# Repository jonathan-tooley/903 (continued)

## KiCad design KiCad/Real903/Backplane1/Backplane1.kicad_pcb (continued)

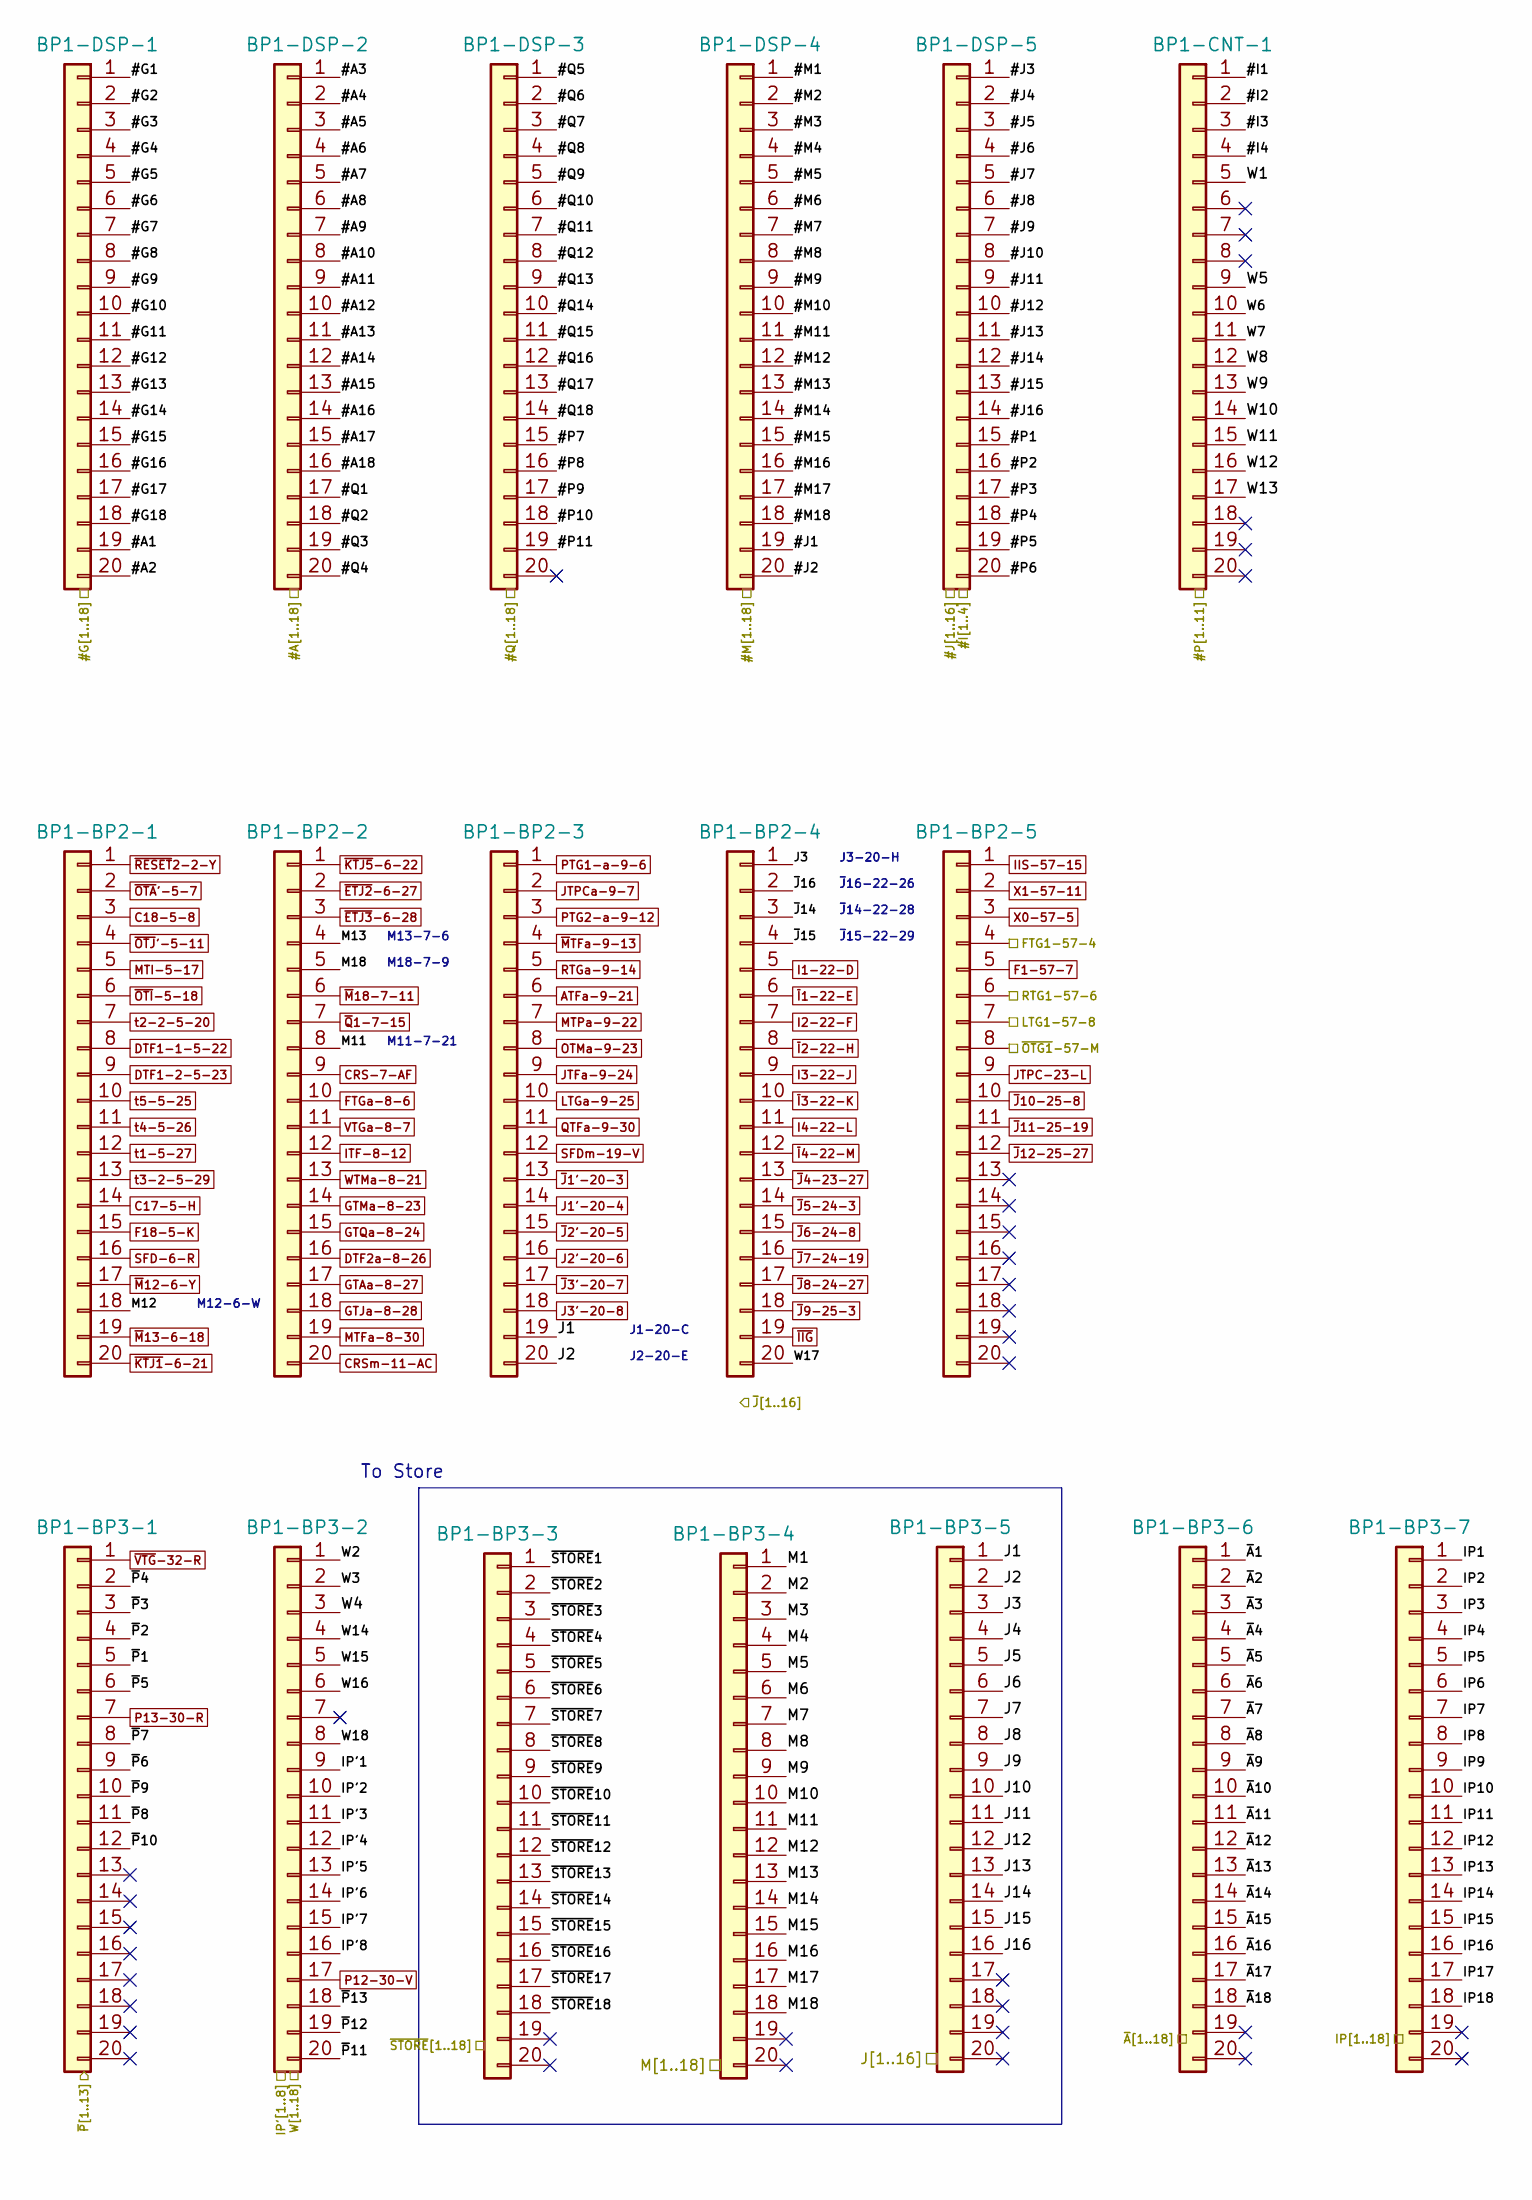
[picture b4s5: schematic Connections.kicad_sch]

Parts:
BP1-BP2-1, BP1-BP2-2, BP1-BP2-3, BP1-BP2-4, BP1-BP2-5, BP1-BP3-1, BP1-BP3-2, BP1-BP3-3, BP1-BP3-4, BP1-BP3-5, BP1-BP3-6, BP1-BP3-7, BP1-CNT-1, BP1-DSP-1, BP1-DSP-2, BP1-DSP-3, BP1-DSP-4, BP1-DSP-5: IDC-Header_2x10_P2.54mm_Latch_Vertical

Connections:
#A1: BP1-DSP-1.19; also elsewhere on the board
#A2: BP1-DSP-1.20; also elsewhere on the board
#A3: BP1-DSP-2.1; also elsewhere on the board
#A4: BP1-DSP-2.2; also elsewhere on the board
#A5: BP1-DSP-2.3; also elsewhere on the board
#A6: BP1-DSP-2.4; also elsewhere on the board
#A7: BP1-DSP-2.5; also elsewhere on the board
#A8: BP1-DSP-2.6; also elsewhere on the board
#A9: BP1-DSP-2.7; also elsewhere on the board
#A10: BP1-DSP-2.8; also elsewhere on the board
#A11: BP1-DSP-2.9; also elsewhere on the board
#A12: BP1-DSP-2.10; also elsewhere on the board
#A13: BP1-DSP-2.11; also elsewhere on the board
#A14: BP1-DSP-2.12; also elsewhere on the board
#A15: BP1-DSP-2.13; also elsewhere on the board
#A16: BP1-DSP-2.14; also elsewhere on the board
#A17: BP1-DSP-2.15; also elsewhere on the board
#A18: BP1-DSP-2.16; also elsewhere on the board
#G1: BP1-DSP-1.1; also elsewhere on the board
#G2: BP1-DSP-1.2; also elsewhere on the board
#G3: BP1-DSP-1.3; also elsewhere on the board
#G4: BP1-DSP-1.4; also elsewhere on the board
#G5: BP1-DSP-1.5; also elsewhere on the board
#G6: BP1-DSP-1.6; also elsewhere on the board
#G7: BP1-DSP-1.7; also elsewhere on the board
#G8: BP1-DSP-1.8; also elsewhere on the board
#G9: BP1-DSP-1.9; also elsewhere on the board
#G10: BP1-DSP-1.10; also elsewhere on the board
#G11: BP1-DSP-1.11; also elsewhere on the board
#G12: BP1-DSP-1.12; also elsewhere on the board
#G13: BP1-DSP-1.13; also elsewhere on the board
#G14: BP1-DSP-1.14; also elsewhere on the board
#G15: BP1-DSP-1.15; also elsewhere on the board
#G16: BP1-DSP-1.16; also elsewhere on the board
#G17: BP1-DSP-1.17; also elsewhere on the board
#G18: BP1-DSP-1.18; also elsewhere on the board
#I1: BP1-CNT-1.1; also elsewhere on the board
#I2: BP1-CNT-1.2; also elsewhere on the board
#I3: BP1-CNT-1.3; also elsewhere on the board
#I4: BP1-CNT-1.4; also elsewhere on the board
#J1: BP1-DSP-4.19; also elsewhere on the board
#J2: BP1-DSP-4.20; also elsewhere on the board
#J3: BP1-DSP-5.1; also elsewhere on the board
#J4: BP1-DSP-5.2; also elsewhere on the board
#J5: BP1-DSP-5.3; also elsewhere on the board
#J6: BP1-DSP-5.4; also elsewhere on the board
#J7: BP1-DSP-5.5; also elsewhere on the board
#J8: BP1-DSP-5.6; also elsewhere on the board
#J9: BP1-DSP-5.7; also elsewhere on the board
#J10: BP1-DSP-5.8; also elsewhere on the board
#J11: BP1-DSP-5.9; also elsewhere on the board
#J12: BP1-DSP-5.10; also elsewhere on the board
#J13: BP1-DSP-5.11; also elsewhere on the board
#J14: BP1-DSP-5.12; also elsewhere on the board
#J15: BP1-DSP-5.13; also elsewhere on the board
#J16: BP1-DSP-5.14; also elsewhere on the board
#M1: BP1-DSP-4.1; also elsewhere on the board
#M2: BP1-DSP-4.2; also elsewhere on the board
#M3: BP1-DSP-4.3; also elsewhere on the board
#M4: BP1-DSP-4.4; also elsewhere on the board
#M5: BP1-DSP-4.5; also elsewhere on the board
#M6: BP1-DSP-4.6; also elsewhere on the board
#M7: BP1-DSP-4.7; also elsewhere on the board
#M8: BP1-DSP-4.8; also elsewhere on the board
#M9: BP1-DSP-4.9; also elsewhere on the board
#M10: BP1-DSP-4.10; also elsewhere on the board
#M11: BP1-DSP-4.11; also elsewhere on the board
#M12: BP1-DSP-4.12; also elsewhere on the board
#M13: BP1-DSP-4.13; also elsewhere on the board
#M14: BP1-DSP-4.14; also elsewhere on the board
#M15: BP1-DSP-4.15; also elsewhere on the board
#M16: BP1-DSP-4.16; also elsewhere on the board
#M17: BP1-DSP-4.17; also elsewhere on the board
#M18: BP1-DSP-4.18; also elsewhere on the board
#P1: BP1-DSP-5.15; also elsewhere on the board
#P2: BP1-DSP-5.16; also elsewhere on the board
#P3: BP1-DSP-5.17; also elsewhere on the board
#P4: BP1-DSP-5.18; also elsewhere on the board
#P5: BP1-DSP-5.19; also elsewhere on the board
#P6: BP1-DSP-5.20; also elsewhere on the board
#P7: BP1-DSP-3.15; also elsewhere on the board
#P8: BP1-DSP-3.16; also elsewhere on the board
#P9: BP1-DSP-3.17; also elsewhere on the board
#P10: BP1-DSP-3.18; also elsewhere on the board
#P11: BP1-DSP-3.19; also elsewhere on the board
#Q1: BP1-DSP-2.17; also elsewhere on the board
#Q2: BP1-DSP-2.18; also elsewhere on the board
#Q3: BP1-DSP-2.19; also elsewhere on the board
#Q4: BP1-DSP-2.20; also elsewhere on the board
#Q5: BP1-DSP-3.1; also elsewhere on the board
#Q6: BP1-DSP-3.2; also elsewhere on the board
#Q7: BP1-DSP-3.3; also elsewhere on the board
#Q8: BP1-DSP-3.4; also elsewhere on the board
#Q9: BP1-DSP-3.5; also elsewhere on the board
#Q10: BP1-DSP-3.6; also elsewhere on the board
#Q11: BP1-DSP-3.7; also elsewhere on the board
#Q12: BP1-DSP-3.8; also elsewhere on the board
#Q13: BP1-DSP-3.9; also elsewhere on the board
#Q14: BP1-DSP-3.10; also elsewhere on the board
#Q15: BP1-DSP-3.11; also elsewhere on the board
#Q16: BP1-DSP-3.12; also elsewhere on the board
#Q17: BP1-DSP-3.13; also elsewhere on the board
#Q18: BP1-DSP-3.14; also elsewhere on the board
/Connections/~J14: BP1-BP2-4.3; also elsewhere on the board
/Connections/~J15: BP1-BP2-4.4; also elsewhere on the board
/Connections/~J16: BP1-BP2-4.2; also elsewhere on the board
/Low.FTG: BP1-BP2-5.4; also elsewhere on the board
/Low.LTG: BP1-BP2-5.7; also elsewhere on the board
/Low.RTG: BP1-BP2-5.6; also elsewhere on the board
/Low.~OTG: BP1-BP2-5.8; also elsewhere on the board
ATFa-9-21: BP1-BP2-3.6; also elsewhere on the board
C17-5-H: BP1-BP2-1.14; also elsewhere on the board
C18-5-8: BP1-BP2-1.3; also elsewhere on the board
CRS-7-AF: BP1-BP2-2.9; also elsewhere on the board
CRSm-11-AC: BP1-BP2-2.20; also elsewhere on the board
DTF1-1-5-22: BP1-BP2-1.8; also elsewhere on the board
DTF1-2-5-23: BP1-BP2-1.9; also elsewhere on the board
DTF2a-8-26: BP1-BP2-2.16; also elsewhere on the board
F1-57-7: BP1-BP2-5.5; also elsewhere on the board
F18-5-K: BP1-BP2-1.15; also elsewhere on the board
FTGa-8-6: BP1-BP2-2.10; also elsewhere on the board
GTAa-8-27: BP1-BP2-2.17; also elsewhere on the board
GTJa-8-28: BP1-BP2-2.18; also elsewhere on the board
GTMa-8-23: BP1-BP2-2.14; also elsewhere on the board
GTQa-8-24: BP1-BP2-2.15; also elsewhere on the board
I1-22-D: BP1-BP2-4.5; also elsewhere on the board
I2-22-F: BP1-BP2-4.7; also elsewhere on the board
I3-22-J: BP1-BP2-4.9; also elsewhere on the board
I4-22-L: BP1-BP2-4.11; also elsewhere on the board
IIS-57-15: BP1-BP2-5.1; also elsewhere on the board
IP1: BP1-BP3-7.1; also elsewhere on the board
IP2: BP1-BP3-7.2; also elsewhere on the board
IP3: BP1-BP3-7.3; also elsewhere on the board
IP4: BP1-BP3-7.4; also elsewhere on the board
IP5: BP1-BP3-7.5; also elsewhere on the board
IP6: BP1-BP3-7.6; also elsewhere on the board
IP7: BP1-BP3-7.7; also elsewhere on the board
IP8: BP1-BP3-7.8; also elsewhere on the board
IP9: BP1-BP3-7.9; also elsewhere on the board
IP10: BP1-BP3-7.10; also elsewhere on the board
IP11: BP1-BP3-7.11; also elsewhere on the board
IP12: BP1-BP3-7.12; also elsewhere on the board
IP13: BP1-BP3-7.13; also elsewhere on the board
IP14: BP1-BP3-7.14; also elsewhere on the board
IP15: BP1-BP3-7.15; also elsewhere on the board
IP16: BP1-BP3-7.16; also elsewhere on the board
IP17: BP1-BP3-7.17; also elsewhere on the board
IP18: BP1-BP3-7.18; also elsewhere on the board
IP'1: BP1-BP3-2.9; also elsewhere on the board
IP'2: BP1-BP3-2.10; also elsewhere on the board
IP'3: BP1-BP3-2.11; also elsewhere on the board
IP'4: BP1-BP3-2.12; also elsewhere on the board
IP'5: BP1-BP3-2.13; also elsewhere on the board
IP'6: BP1-BP3-2.14; also elsewhere on the board
IP'7: BP1-BP3-2.15; also elsewhere on the board
IP'8: BP1-BP3-2.16; also elsewhere on the board
ITF-8-12: BP1-BP2-2.12; also elsewhere on the board
J1: BP1-BP2-3.19, BP1-BP3-5.1; also elsewhere on the board
J1'-20-4: BP1-BP2-3.14; also elsewhere on the board
J2: BP1-BP2-3.20, BP1-BP3-5.2; also elsewhere on the board
J2'-20-6: BP1-BP2-3.16; also elsewhere on the board
J3: BP1-BP2-4.1, BP1-BP3-5.3; also elsewhere on the board
J3'-20-8: BP1-BP2-3.18; also elsewhere on the board
J4: BP1-BP3-5.4; also elsewhere on the board
J5: BP1-BP3-5.5; also elsewhere on the board
J6: BP1-BP3-5.6; also elsewhere on the board
J7: BP1-BP3-5.7; also elsewhere on the board
J8: BP1-BP3-5.8; also elsewhere on the board
J9: BP1-BP3-5.9; also elsewhere on the board
J10: BP1-BP3-5.10; also elsewhere on the board
J11: BP1-BP3-5.11; also elsewhere on the board
J12: BP1-BP3-5.12; also elsewhere on the board
J13: BP1-BP3-5.13; also elsewhere on the board
J14: BP1-BP3-5.14; also elsewhere on the board
J15: BP1-BP3-5.15; also elsewhere on the board
J16: BP1-BP3-5.16; also elsewhere on the board
JTFa-9-24: BP1-BP2-3.9; also elsewhere on the board
JTPC-23-L: BP1-BP2-5.9; also elsewhere on the board
JTPCa-9-7: BP1-BP2-3.2; also elsewhere on the board
LTGa-9-25: BP1-BP2-3.10; also elsewhere on the board
M1: BP1-BP3-4.1; also elsewhere on the board
M2: BP1-BP3-4.2; also elsewhere on the board
M3: BP1-BP3-4.3; also elsewhere on the board
M4: BP1-BP3-4.4; also elsewhere on the board
M5: BP1-BP3-4.5; also elsewhere on the board
M6: BP1-BP3-4.6; also elsewhere on the board
M7: BP1-BP3-4.7; also elsewhere on the board
M8: BP1-BP3-4.8; also elsewhere on the board
M9: BP1-BP3-4.9; also elsewhere on the board
M10: BP1-BP3-4.10; also elsewhere on the board
M11: BP1-BP2-2.8, BP1-BP3-4.11; also elsewhere on the board
M12: BP1-BP2-1.18, BP1-BP3-4.12; also elsewhere on the board
M13: BP1-BP2-2.4, BP1-BP3-4.13; also elsewhere on the board
M14: BP1-BP3-4.14; also elsewhere on the board
M15: BP1-BP3-4.15; also elsewhere on the board
M16: BP1-BP3-4.16; also elsewhere on the board
M17: BP1-BP3-4.17; also elsewhere on the board
M18: BP1-BP2-2.5, BP1-BP3-4.18; also elsewhere on the board
MTFa-8-30: BP1-BP2-2.19; also elsewhere on the board
MTI-5-17: BP1-BP2-1.5; also elsewhere on the board
MTPa-9-22: BP1-BP2-3.7; also elsewhere on the board
OTMa-9-23: BP1-BP2-3.8; also elsewhere on the board
P12-30-V: BP1-BP3-2.17; also elsewhere on the board
P13-30-R: BP1-BP3-1.7; also elsewhere on the board
PTG1-a-9-6: BP1-BP2-3.1; also elsewhere on the board
PTG2-a-9-12: BP1-BP2-3.3; also elsewhere on the board
QTFa-9-30: BP1-BP2-3.11; also elsewhere on the board
RTGa-9-14: BP1-BP2-3.5; also elsewhere on the board
SFD-6-R: BP1-BP2-1.16; also elsewhere on the board
SFDm-19-V: BP1-BP2-3.12; also elsewhere on the board
VTGa-8-7: BP1-BP2-2.11; also elsewhere on the board
W1: BP1-CNT-1.5; also elsewhere on the board
W2: BP1-BP3-2.1; also elsewhere on the board
W3: BP1-BP3-2.2; also elsewhere on the board
W4: BP1-BP3-2.3; also elsewhere on the board
W5: BP1-CNT-1.9; also elsewhere on the board
W6: BP1-CNT-1.10; also elsewhere on the board
W7: BP1-CNT-1.11; also elsewhere on the board
W8: BP1-CNT-1.12; also elsewhere on the board
W9: BP1-CNT-1.13; also elsewhere on the board
W10: BP1-CNT-1.14; also elsewhere on the board
W11: BP1-CNT-1.15; also elsewhere on the board
W12: BP1-CNT-1.16; also elsewhere on the board
W13: BP1-CNT-1.17; also elsewhere on the board
W14: BP1-BP3-2.4; also elsewhere on the board
W15: BP1-BP3-2.5; also elsewhere on the board
W16: BP1-BP3-2.6; also elsewhere on the board
W17: BP1-BP2-4.20; also elsewhere on the board
W18: BP1-BP3-2.8; also elsewhere on the board
WTMa-8-21: BP1-BP2-2.13; also elsewhere on the board
X0-57-5: BP1-BP2-5.3; also elsewhere on the board
X1-57-11: BP1-BP2-5.2; also elsewhere on the board
t1-5-27: BP1-BP2-1.12; also elsewhere on the board
t2-2-5-20: BP1-BP2-1.7; also elsewhere on the board
t3-2-5-29: BP1-BP2-1.13; also elsewhere on the board
t4-5-26: BP1-BP2-1.11; also elsewhere on the board
t5-5-25: BP1-BP2-1.10; also elsewhere on the board
~A1: BP1-BP3-6.1; also elsewhere on the board
~A2: BP1-BP3-6.2; also elsewhere on the board
~A3: BP1-BP3-6.3; also elsewhere on the board
~A4: BP1-BP3-6.4; also elsewhere on the board
~A5: BP1-BP3-6.5; also elsewhere on the board
~A6: BP1-BP3-6.6; also elsewhere on the board
~A7: BP1-BP3-6.7; also elsewhere on the board
~A8: BP1-BP3-6.8; also elsewhere on the board
~A9: BP1-BP3-6.9; also elsewhere on the board
~A10: BP1-BP3-6.10; also elsewhere on the board
~A11: BP1-BP3-6.11; also elsewhere on the board
~A12: BP1-BP3-6.12; also elsewhere on the board
~A13: BP1-BP3-6.13; also elsewhere on the board
~A14: BP1-BP3-6.14; also elsewhere on the board
~A15: BP1-BP3-6.15; also elsewhere on the board
~A16: BP1-BP3-6.16; also elsewhere on the board
~A17: BP1-BP3-6.17; also elsewhere on the board
~A18: BP1-BP3-6.18; also elsewhere on the board
~ETJ2-6-27: BP1-BP2-2.2; also elsewhere on the board
~ETJ3-6-28: BP1-BP2-2.3; also elsewhere on the board
~IIG: BP1-BP2-4.19; also elsewhere on the board
~I1-22-E: BP1-BP2-4.6; also elsewhere on the board
~I2-22-H: BP1-BP2-4.8; also elsewhere on the board
~I3-22-K: BP1-BP2-4.10; also elsewhere on the board
~I4-22-M: BP1-BP2-4.12; also elsewhere on the board
~J1'-20-3: BP1-BP2-3.13; also elsewhere on the board
~J2'-20-5: BP1-BP2-3.15; also elsewhere on the board
~J3'-20-7: BP1-BP2-3.17; also elsewhere on the board
~J4-23-27: BP1-BP2-4.13; also elsewhere on the board
~J5-24-3: BP1-BP2-4.14; also elsewhere on the board
~J6-24-8: BP1-BP2-4.15; also elsewhere on the board
~J7-24-19: BP1-BP2-4.16; also elsewhere on the board
~J8-24-27: BP1-BP2-4.17; also elsewhere on the board
~J9-25-3: BP1-BP2-4.18; also elsewhere on the board
~J10-25-8: BP1-BP2-5.10; also elsewhere on the board
~J11-25-19: BP1-BP2-5.11; also elsewhere on the board
~J12-25-27: BP1-BP2-5.12; also elsewhere on the board
~KTJ1-6-21: BP1-BP2-1.20; also elsewhere on the board
~KTJ5-6-22: BP1-BP2-2.1; also elsewhere on the board
~M12-6-Y: BP1-BP2-1.17; also elsewhere on the board
~M13-6-18: BP1-BP2-1.19; also elsewhere on the board
~M18-7-11: BP1-BP2-2.6; also elsewhere on the board
~MTFa-9-13: BP1-BP2-3.4; also elsewhere on the board
~OTA'-5-7: BP1-BP2-1.2; also elsewhere on the board
~OTI-5-18: BP1-BP2-1.6; also elsewhere on the board
~OTJ'-5-11: BP1-BP2-1.4; also elsewhere on the board
~P1: BP1-BP3-1.5; also elsewhere on the board
~P2: BP1-BP3-1.4; also elsewhere on the board
~P3: BP1-BP3-1.3; also elsewhere on the board
~P4: BP1-BP3-1.2; also elsewhere on the board
~P5: BP1-BP3-1.6; also elsewhere on the board
~P6: BP1-BP3-1.9; also elsewhere on the board
~P7: BP1-BP3-1.8; also elsewhere on the board
~P8: BP1-BP3-1.11; also elsewhere on the board
~P9: BP1-BP3-1.10; also elsewhere on the board
~P10: BP1-BP3-1.12; also elsewhere on the board
~P11: BP1-BP3-2.20; also elsewhere on the board
~P12: BP1-BP3-2.19; also elsewhere on the board
~P13: BP1-BP3-2.18; also elsewhere on the board
~Q1-7-15: BP1-BP2-2.7; also elsewhere on the board
~RESET2-2-Y: BP1-BP2-1.1; also elsewhere on the board
~STORE1: BP1-BP3-3.1; also elsewhere on the board
~STORE2: BP1-BP3-3.2; also elsewhere on the board
~STORE3: BP1-BP3-3.3; also elsewhere on the board
~STORE4: BP1-BP3-3.4; also elsewhere on the board
~STORE5: BP1-BP3-3.5; also elsewhere on the board
~STORE6: BP1-BP3-3.6; also elsewhere on the board
~STORE7: BP1-BP3-3.7; also elsewhere on the board
~STORE8: BP1-BP3-3.8; also elsewhere on the board
~STORE9: BP1-BP3-3.9; also elsewhere on the board
~STORE10: BP1-BP3-3.10; also elsewhere on the board
~STORE11: BP1-BP3-3.11; also elsewhere on the board
~STORE12: BP1-BP3-3.12; also elsewhere on the board
~STORE13: BP1-BP3-3.13; also elsewhere on the board
~STORE14: BP1-BP3-3.14; also elsewhere on the board
~STORE15: BP1-BP3-3.15; also elsewhere on the board
~STORE16: BP1-BP3-3.16; also elsewhere on the board
~STORE17: BP1-BP3-3.17; also elsewhere on the board
~STORE18: BP1-BP3-3.18; also elsewhere on the board
~VTG-32-R: BP1-BP3-1.1; also elsewhere on the board

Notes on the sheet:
J3-20-H
M12-6-W
J1-20-C
M13-7-6
M18-7-9
~{J}14-22-28
~{J}16-22-26
J2-20-E
M11-7-21
To Store
~{J}15-22-29

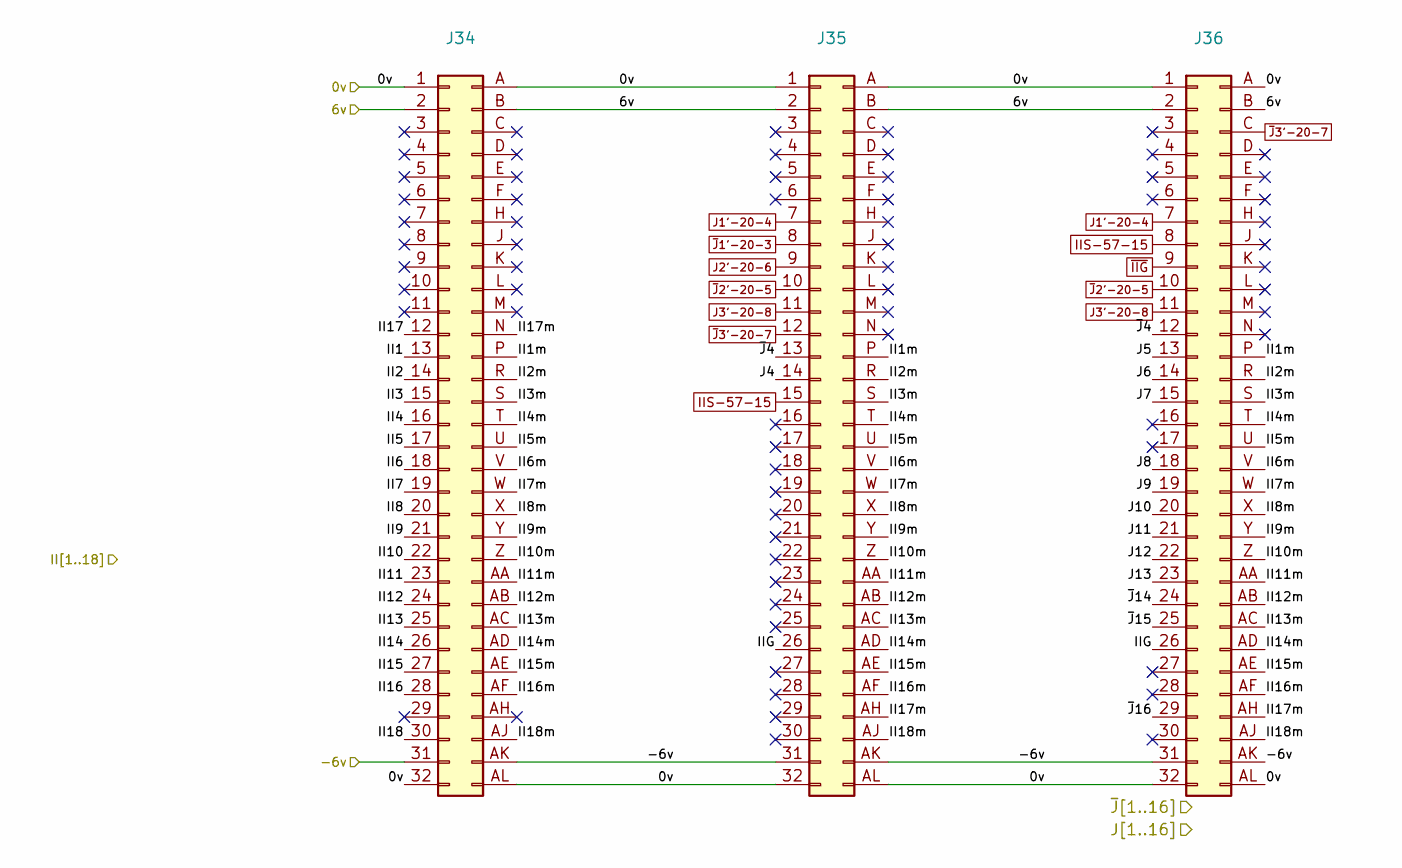
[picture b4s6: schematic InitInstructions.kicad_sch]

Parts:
J34, J35, J36: DIN41612_B_2x32_Vertical

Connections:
0v: J34.1, J34.32, J34.A, J34.AL, J35.1, J35.32, J35.A, J35.AL, J36.1, J36.32, J36.A, J36.AL; also elsewhere on the board
6v: J34.2, J34.B, J35.2, J35.B, J36.2, J36.B; also elsewhere on the board
/Connections/~J4: J35.13, J36.12
/Connections/~J14: J36.24; also elsewhere on the board
/Connections/~J15: J36.25; also elsewhere on the board
/Connections/~J16: J36.29; also elsewhere on the board
/InitInstructions/II1m: J34.P, J35.P, J36.P
/InitInstructions/II2m: J34.R, J35.R, J36.R
/InitInstructions/II3m: J34.S, J35.S, J36.S
/InitInstructions/II4m: J34.T, J35.T, J36.T
/InitInstructions/II5m: J34.U, J35.U, J36.U
/InitInstructions/II6m: J34.V, J35.V, J36.V
/InitInstructions/II7m: J34.W, J35.W, J36.W
/InitInstructions/II8m: J34.X, J35.X, J36.X
/InitInstructions/II9m: J34.Y, J35.Y, J36.Y
/InitInstructions/II10m: J34.Z, J35.Z, J36.Z
/InitInstructions/II11m: J34.AA, J35.AA, J36.AA
/InitInstructions/II12m: J34.AB, J35.AB, J36.AB
/InitInstructions/II13m: J34.AC, J35.AC, J36.AC
/InitInstructions/II14m: J34.AD, J35.AD, J36.AD
/InitInstructions/II15m: J34.AE, J35.AE, J36.AE
/InitInstructions/II16m: J34.AF, J35.AF, J36.AF
/InitInstructions/II17m: J34.N, J35.AH, J36.AH
/InitInstructions/II18m: J34.AJ, J35.AJ, J36.AJ
/InitInstructions/IIG: J35.26, J36.26
II1: J34.13; also elsewhere on the board
II2: J34.14; also elsewhere on the board
II3: J34.15; also elsewhere on the board
II4: J34.16; also elsewhere on the board
II5: J34.17; also elsewhere on the board
II6: J34.18; also elsewhere on the board
II7: J34.19; also elsewhere on the board
II8: J34.20; also elsewhere on the board
II9: J34.21; also elsewhere on the board
II10: J34.22; also elsewhere on the board
II11: J34.23; also elsewhere on the board
II12: J34.24; also elsewhere on the board
II13: J34.25; also elsewhere on the board
II14: J34.26; also elsewhere on the board
II15: J34.27; also elsewhere on the board
II16: J34.28; also elsewhere on the board
II17: J34.12; also elsewhere on the board
II18: J34.30; also elsewhere on the board
IIS-57-15: J35.15, J36.8; also elsewhere on the board
J1'-20-4: J35.7, J36.7; also elsewhere on the board
J2'-20-6: J35.9; also elsewhere on the board
J3'-20-8: J35.11, J36.11; also elsewhere on the board
J4: J35.14; also elsewhere on the board
J5: J36.13; also elsewhere on the board
J6: J36.14; also elsewhere on the board
J7: J36.15; also elsewhere on the board
J8: J36.18; also elsewhere on the board
J9: J36.19; also elsewhere on the board
J10: J36.20; also elsewhere on the board
J11: J36.21; also elsewhere on the board
J12: J36.22; also elsewhere on the board
J13: J36.23; also elsewhere on the board
Neg6v: J34.31, J34.AK, J35.31, J35.AK, J36.31, J36.AK; also elsewhere on the board
~IIG: J36.9; also elsewhere on the board
~J1'-20-3: J35.8; also elsewhere on the board
~J2'-20-5: J35.10, J36.10; also elsewhere on the board
~J3'-20-7: J35.12, J36.C; also elsewhere on the board

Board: 4 copper layers, 80 parts (23 on the bottom side), 445 nets, no tracks yet.

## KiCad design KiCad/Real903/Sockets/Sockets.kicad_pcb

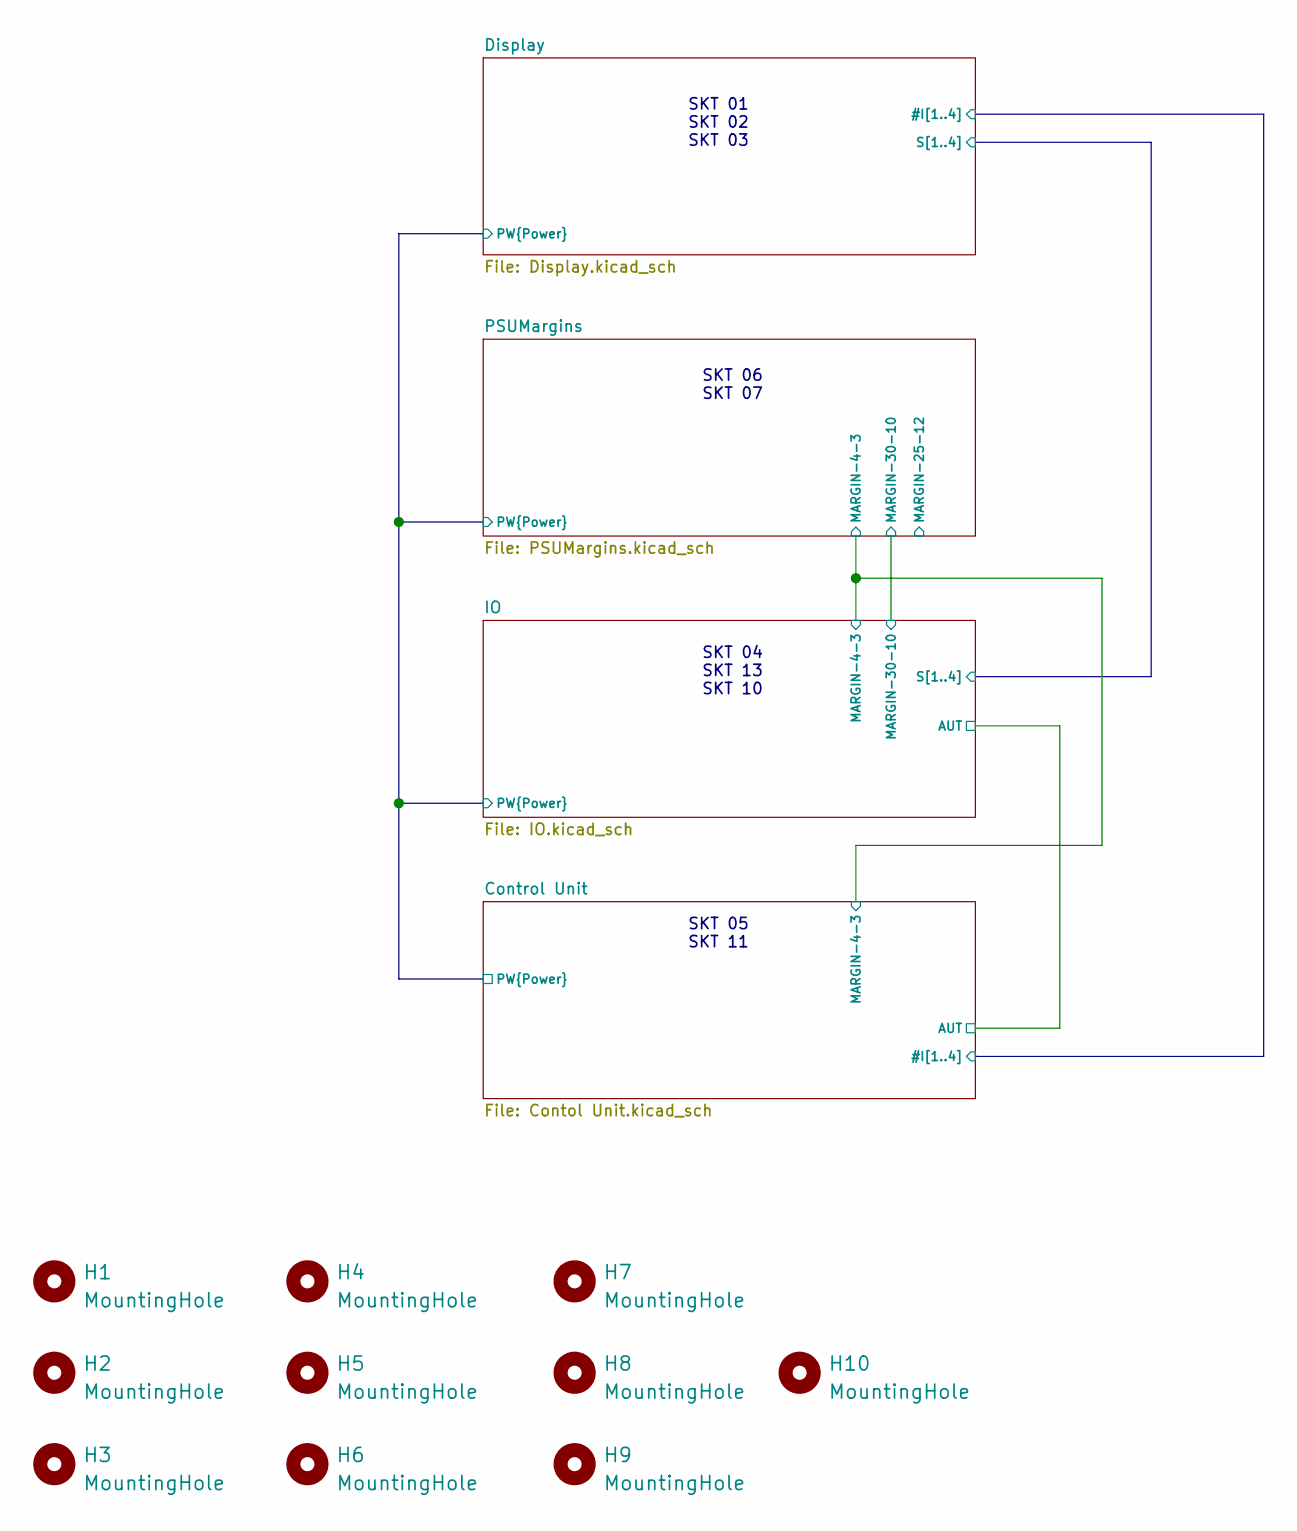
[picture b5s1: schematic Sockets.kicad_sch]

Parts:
H1, H2, H3, H4: MountingHole; MC61_Hole
H5, H10: MountingHole; MC19_Hole
H6, H7: MountingHole; MC41_Hole
H8, H9: MountingHole; MC32_Hole

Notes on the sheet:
SKT 04 SKT 13 SKT 10
SKT 06 SKT 07
SKT 01 SKT 02 SKT 03
SKT 05 SKT 11

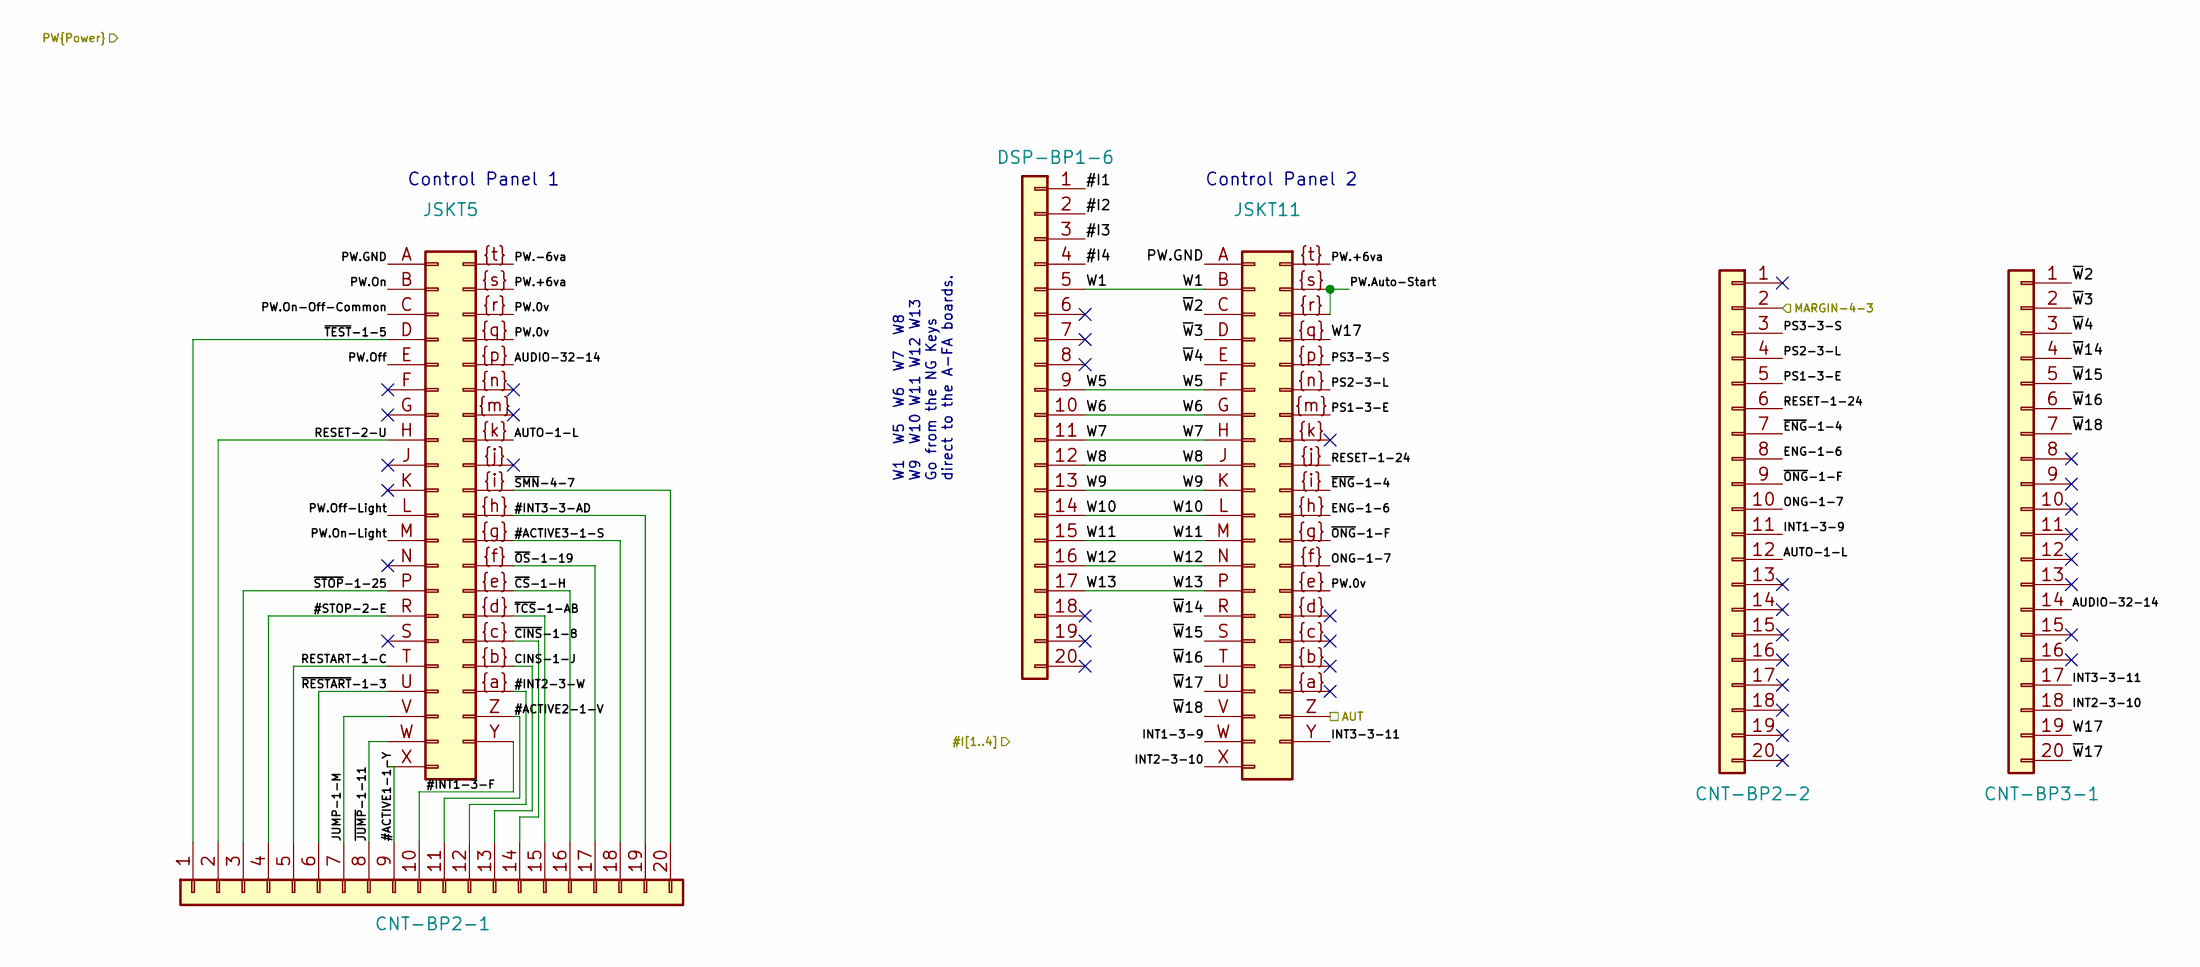
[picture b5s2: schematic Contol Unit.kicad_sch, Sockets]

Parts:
CNT-BP2-1, CNT-BP2-2, CNT-BP3-1: IDC-Header_2x10_P2.54mm_Vertical
DSP-BP1-6: IDC-Header_2x10_P2.54mm_Vertical
JSKT5, JSKT11: MC41

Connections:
/Control Unit/#ACTIVE1-1-Y: CNT-BP2-1.9, JSKT5.X
/Control Unit/#ACTIVE2-1-V: CNT-BP2-1.11, JSKT5.Z
/Control Unit/#ACTIVE3-1-S: CNT-BP2-1.18, JSKT5.~{g}
/Control Unit/#I1: DSP-BP1-6.1; also elsewhere on the board
/Control Unit/#I2: DSP-BP1-6.2; also elsewhere on the board
/Control Unit/#I3: DSP-BP1-6.3; also elsewhere on the board
/Control Unit/#I4: DSP-BP1-6.4; also elsewhere on the board
/Control Unit/#INT1-3-F: CNT-BP2-1.10, JSKT5.Y
/Control Unit/#INT2-3-W: CNT-BP2-1.12, JSKT5.~{a}
/Control Unit/#INT3-3-AD: CNT-BP2-1.19, JSKT5.~{h}
/Control Unit/#STOP-2-E: CNT-BP2-1.4, JSKT5.R
/Control Unit/AUDIO-32-14: CNT-BP3-1.14, JSKT5.~{p}
/Control Unit/AUT: JSKT11.Z; also elsewhere on the board
/Control Unit/AUTO-1-L: CNT-BP2-2.12, JSKT5.~{k}
/Control Unit/CINS-1-J: CNT-BP2-1.13, JSKT5.~{b}
/Control Unit/ENG-1-6: CNT-BP2-2.8, JSKT11.~{h}
/Control Unit/INT1-3-9: CNT-BP2-2.11, JSKT11.W
/Control Unit/INT2-3-10: CNT-BP3-1.18, JSKT11.X
/Control Unit/INT3-3-11: CNT-BP3-1.17, JSKT11.Y
/Control Unit/JUMP-1-M: CNT-BP2-1.7, JSKT5.V
/Control Unit/MARGIN-4-3: CNT-BP2-2.2; also elsewhere on the board
/Control Unit/ONG-1-7: CNT-BP2-2.10, JSKT11.~{f}
/Control Unit/PS1-3-E: CNT-BP2-2.5, JSKT11.~{m}
/Control Unit/PS2-3-L: CNT-BP2-2.4, JSKT11.~{n}
/Control Unit/PS3-3-S: CNT-BP2-2.3, JSKT11.~{p}
/Control Unit/PW.0v: JSKT5.~{q}, JSKT5.~{r}, JSKT11.~{e}; also elsewhere on the board
/Control Unit/PW.+6va: JSKT5.~{s}, JSKT11.~{t}; also elsewhere on the board
/Control Unit/PW.-6va: JSKT5.~{t}; also elsewhere on the board
/Control Unit/PW.Auto-Start: JSKT11.~{r}, JSKT11.~{s}; also elsewhere on the board
/Control Unit/PW.GND: JSKT5.A, JSKT11.A; also elsewhere on the board
/Control Unit/PW.Off: JSKT5.E; also elsewhere on the board
/Control Unit/PW.Off-Light: JSKT5.L; also elsewhere on the board
/Control Unit/PW.On: JSKT5.B; also elsewhere on the board
/Control Unit/PW.On-Light: JSKT5.M; also elsewhere on the board
/Control Unit/PW.On-Off-Common: JSKT5.C; also elsewhere on the board
/Control Unit/RESET-1-24: CNT-BP2-2.6, JSKT11.~{j}
/Control Unit/RESET-2-U: CNT-BP2-1.2, JSKT5.H
/Control Unit/RESTART-1-C: CNT-BP2-1.5, JSKT5.T
/Control Unit/W1: DSP-BP1-6.5, JSKT11.B
/Control Unit/W5: DSP-BP1-6.9, JSKT11.F
/Control Unit/W6: DSP-BP1-6.10, JSKT11.G
/Control Unit/W7: DSP-BP1-6.11, JSKT11.H
/Control Unit/W8: DSP-BP1-6.12, JSKT11.J
/Control Unit/W9: DSP-BP1-6.13, JSKT11.K
/Control Unit/W10: DSP-BP1-6.14, JSKT11.L
/Control Unit/W11: DSP-BP1-6.15, JSKT11.M
/Control Unit/W12: DSP-BP1-6.16, JSKT11.N
/Control Unit/W13: DSP-BP1-6.17, JSKT11.P
/Control Unit/W17: CNT-BP3-1.19, JSKT11.~{q}
/Control Unit/~CINS-1-8: CNT-BP2-1.14, JSKT5.~{c}
/Control Unit/~CS-1-H: CNT-BP2-1.16, JSKT5.~{e}
/Control Unit/~ENG-1-4: CNT-BP2-2.7, JSKT11.~{i}
/Control Unit/~JUMP-1-11: CNT-BP2-1.8, JSKT5.W
/Control Unit/~ONG-1-F: CNT-BP2-2.9, JSKT11.~{g}
/Control Unit/~OS-1-19: CNT-BP2-1.17, JSKT5.~{f}
/Control Unit/~RESTART-1-3: CNT-BP2-1.6, JSKT5.U
/Control Unit/~SMN-4-7: CNT-BP2-1.20, JSKT5.~{i}
/Control Unit/~STOP-1-25: CNT-BP2-1.3, JSKT5.P
/Control Unit/~TCS-1-AB: CNT-BP2-1.15, JSKT5.~{d}
/Control Unit/~TEST-1-5: CNT-BP2-1.1, JSKT5.D
/Control Unit/~W2: CNT-BP3-1.1, JSKT11.C
/Control Unit/~W3: CNT-BP3-1.2, JSKT11.D
/Control Unit/~W4: CNT-BP3-1.3, JSKT11.E
/Control Unit/~W14: CNT-BP3-1.4, JSKT11.R
/Control Unit/~W15: CNT-BP3-1.5, JSKT11.S
/Control Unit/~W16: CNT-BP3-1.6, JSKT11.T
/Control Unit/~W17: CNT-BP3-1.20, JSKT11.U
/Control Unit/~W18: CNT-BP3-1.7, JSKT11.V

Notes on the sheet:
W1 W5 W6 W7 W8 W9 W10 W11 W12 W13 Go from the NG Keys direct to the A-FA boards.
Control Panel 1
Control Panel 2
